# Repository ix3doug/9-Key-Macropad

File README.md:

# 9-Key-Macropad
A 9 Key Macropad for use with F13-F22 key functions. Powered by an RP2040 Microcontroller

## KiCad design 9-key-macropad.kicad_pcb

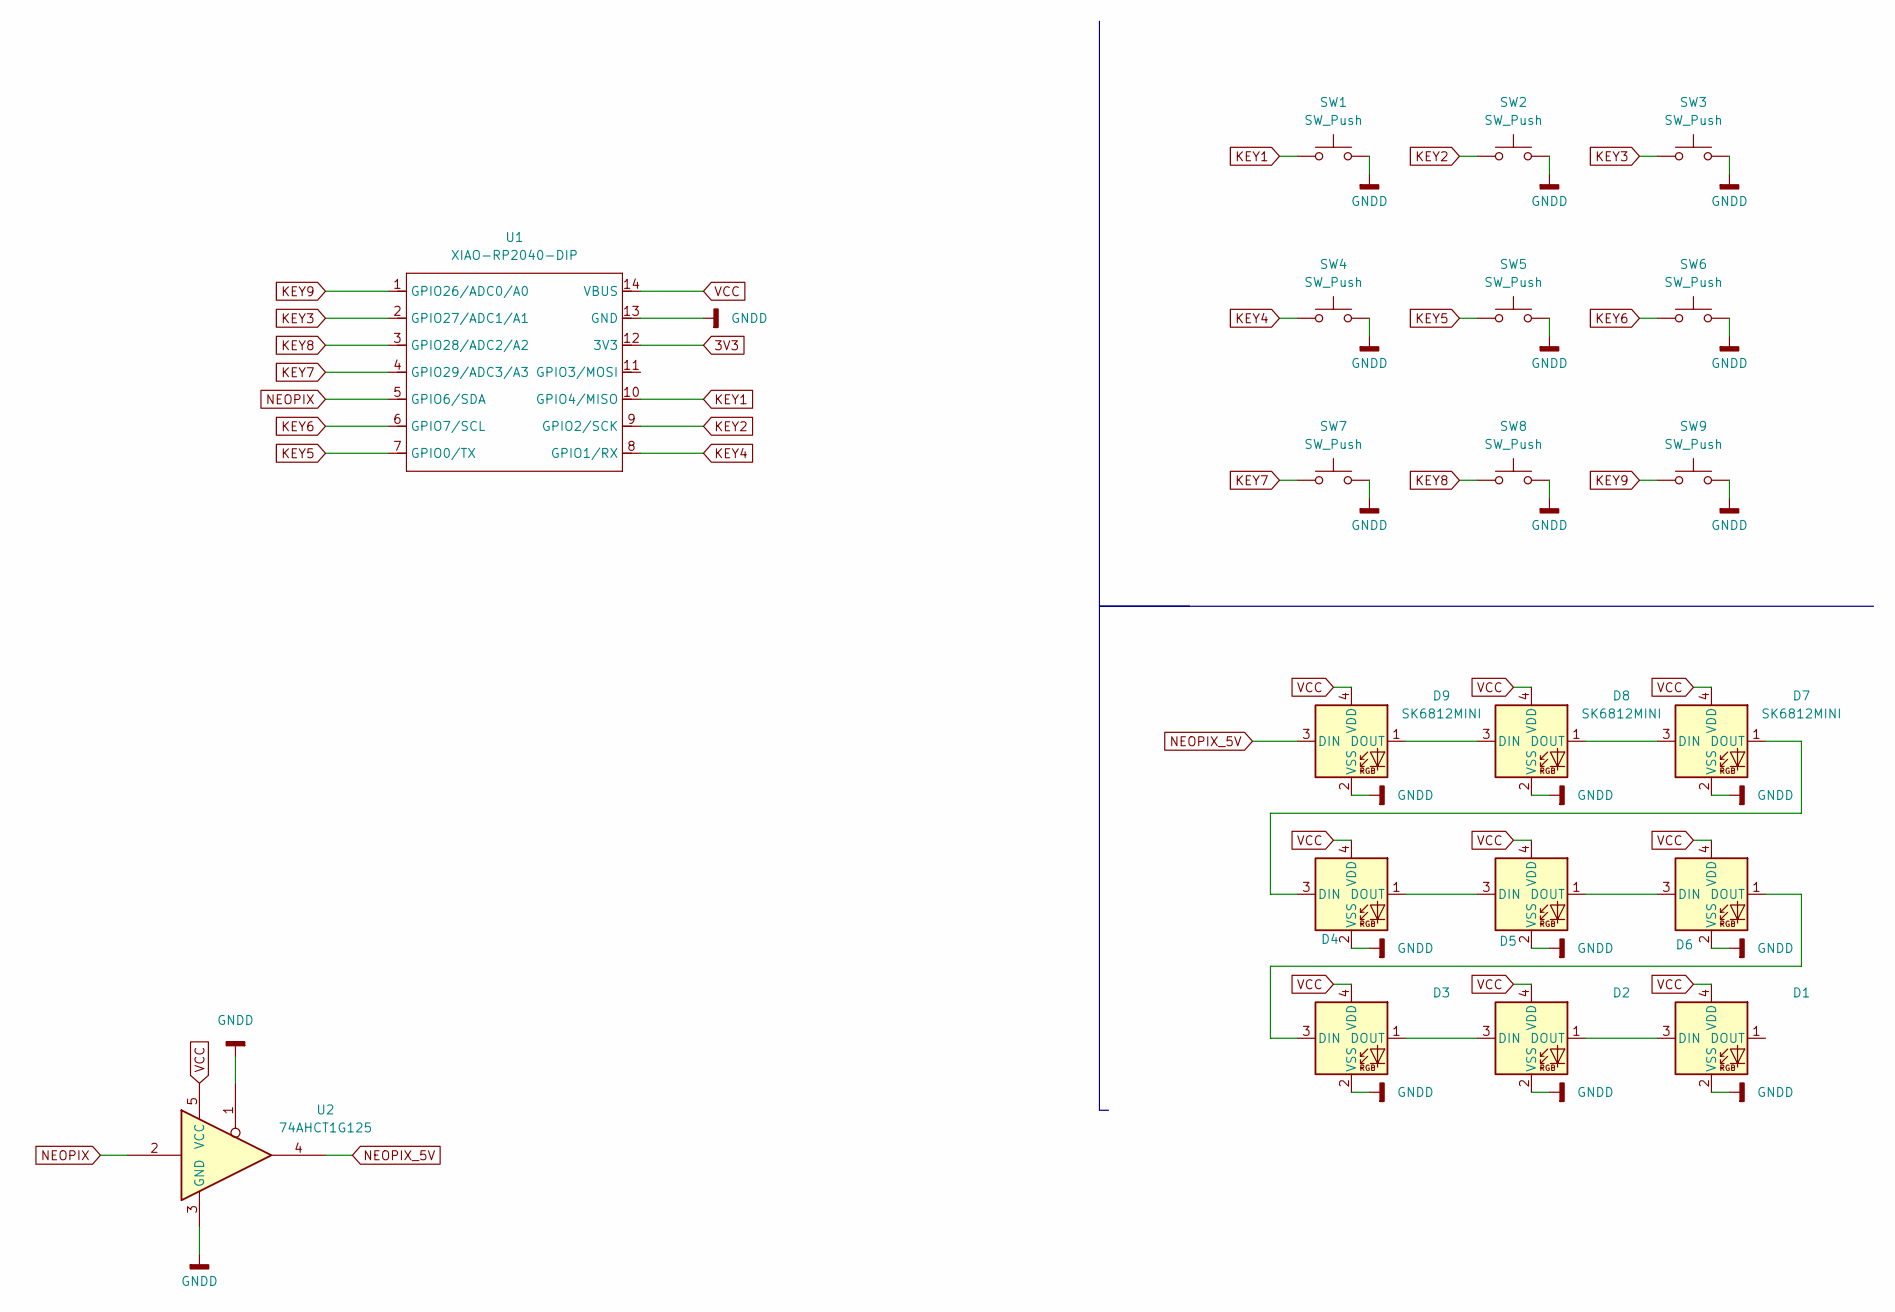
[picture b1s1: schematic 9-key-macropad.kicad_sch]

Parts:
D1, D2, D3, D4, D5, D6, D7, D8, D9: SK6812MINI; LED_SK6812MINI_PLCC4_3.5x3.5mm_P1.75mm
SW1, SW2, SW3, SW4, SW5, SW6, SW7, SW8, SW9: SW_Push; SW_Cherry_MX_1.00u_Plate
U1: XIAO-RP2040-DIP
U2: 74AHCT1G125; SOT95P280X145-5N

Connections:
3V3: U1.12 (3V3)
GNDD: D1.2 (VSS), D2.2 (VSS), D3.2 (VSS), D4.2 (VSS), D5.2 (VSS), D6.2 (VSS), D7.2 (VSS), D8.2 (VSS), D9.2 (VSS), SW1.2, SW2.2, SW3.2, SW4.2, SW5.2, SW6.2, SW7.2, SW8.2, SW9.2, U1.13 (GND), U2.1, U2.3 (GND)
KEY1: SW1.1, U1.10 (GPIO4/MISO)
KEY2: SW2.1, U1.9 (GPIO2/SCK)
KEY3: SW3.1, U1.2 (GPIO27/ADC1/A1)
KEY4: SW4.1, U1.8 (GPIO1/RX)
KEY5: SW5.1, U1.7 (GPIO0/TX)
KEY6: SW6.1, U1.6 (GPIO7/SCL)
KEY7: SW7.1, U1.4 (GPIO29/ADC3/A3)
KEY8: SW8.1, U1.3 (GPIO28/ADC2/A2)
KEY9: SW9.1, U1.1 (GPIO26/ADC0/A0)
NEOPIX: U1.5 (GPIO6/SDA), U2.2
NEOPIX_5V: D9.3 (DIN), U2.4
unnamed: D1.3 (DIN), D2.1 (DOUT)
unnamed: D2.3 (DIN), D3.1 (DOUT)
unnamed: D3.3 (DIN), D6.1 (DOUT)
unnamed: D4.3 (DIN), D7.1 (DOUT)
unnamed: D4.1 (DOUT), D5.3 (DIN)
unnamed: D5.1 (DOUT), D6.3 (DIN)
unnamed: D7.3 (DIN), D8.1 (DOUT)
unnamed: D8.3 (DIN), D9.1 (DOUT)
VCC: D1.4 (VDD), D2.4 (VDD), D3.4 (VDD), D4.4 (VDD), D5.4 (VDD), D6.4 (VDD), D7.4 (VDD), D8.4 (VDD), D9.4 (VDD), U1.14 (VBUS), U2.5 (VCC)

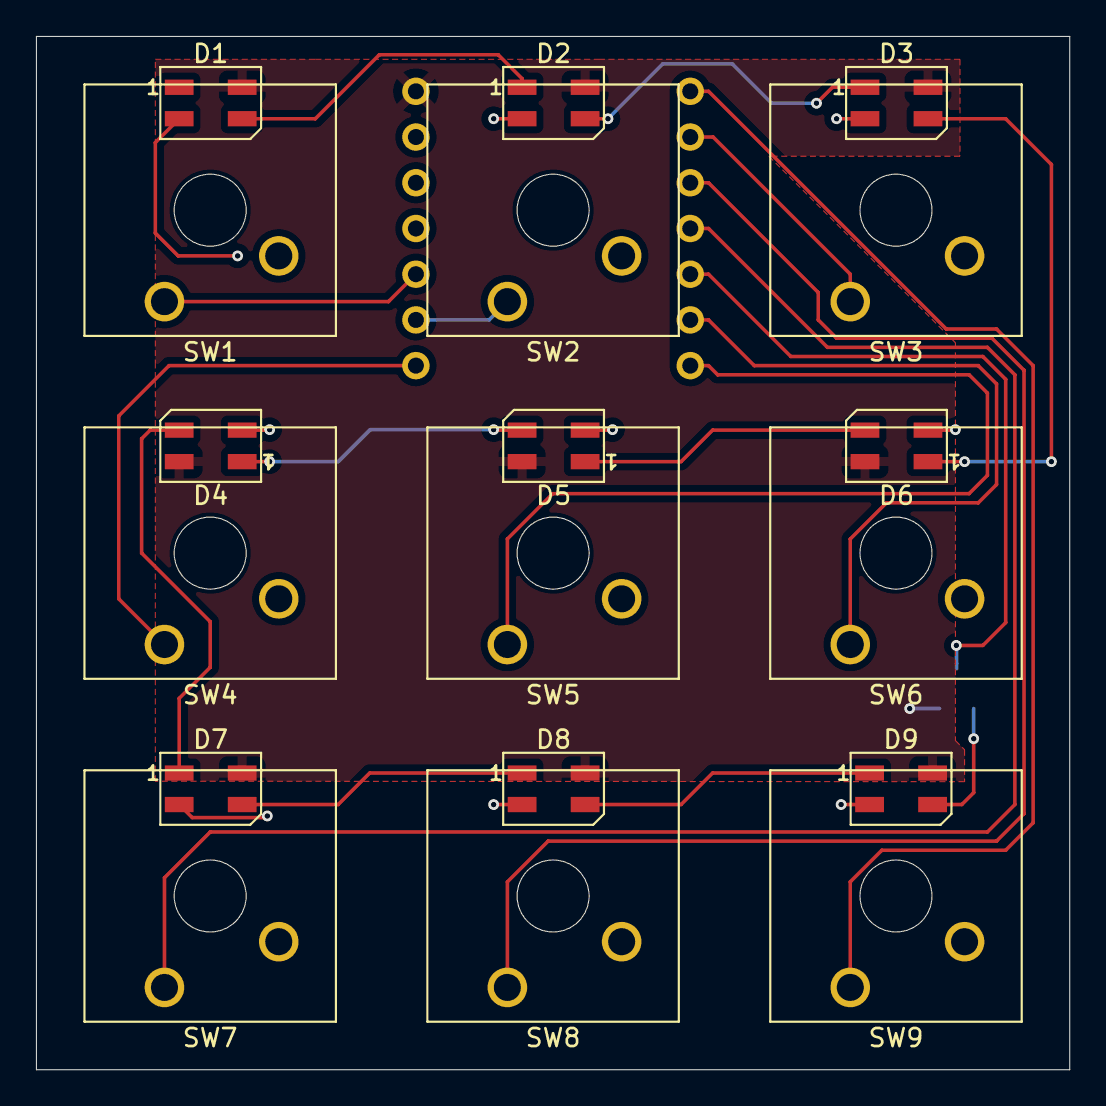
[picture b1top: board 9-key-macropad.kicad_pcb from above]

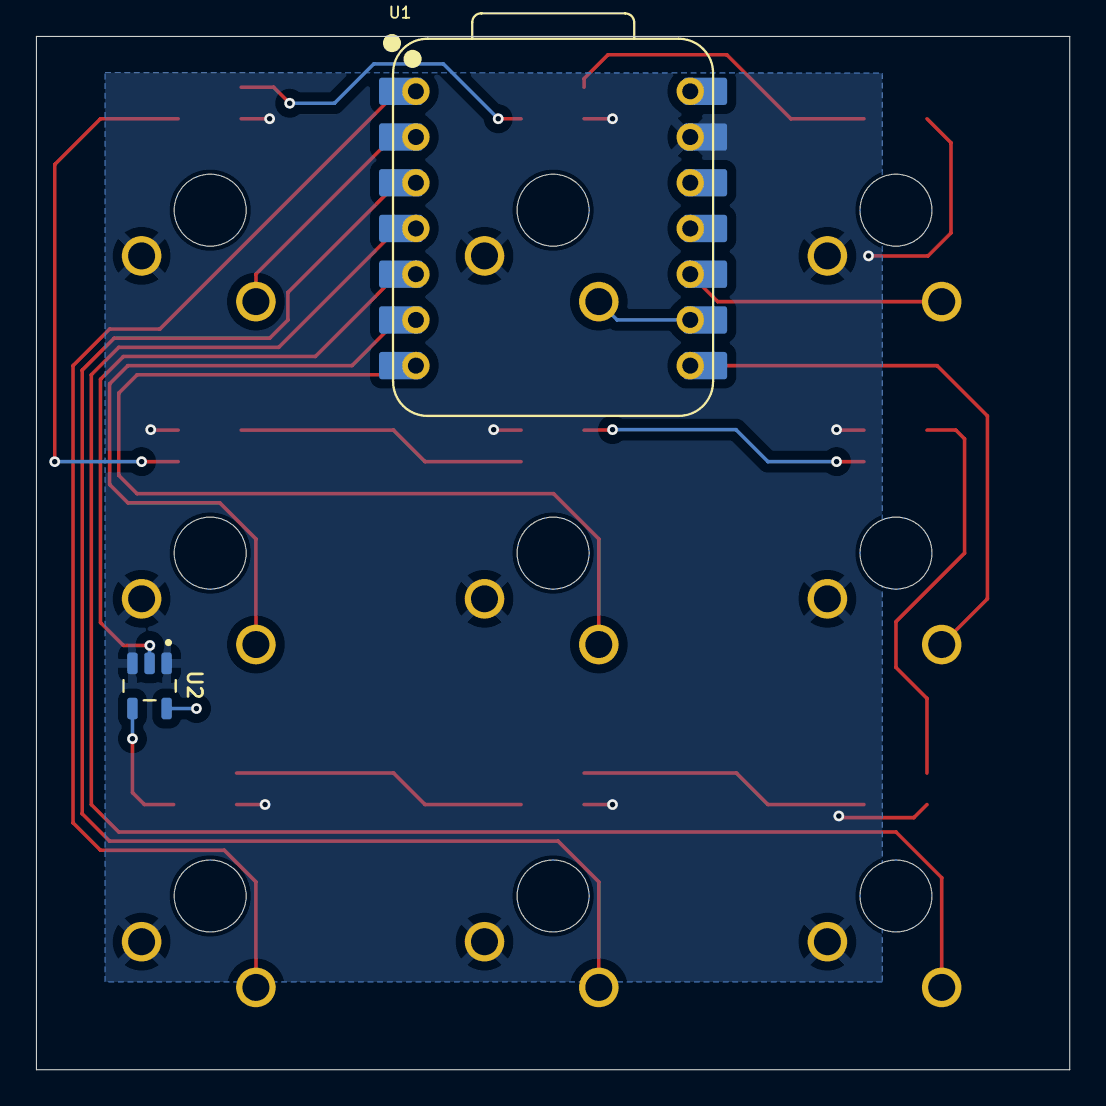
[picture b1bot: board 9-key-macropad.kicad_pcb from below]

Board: 2 copper layers, 57.4 x 57.4 mm, 20 parts (2 on the bottom side), 21 nets.

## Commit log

2025-09-22 Create LICENSE
2025-09-22 Add initial 9-key-macropad KiCad project files and Submodules
    Added schematic, PCB, and project files for the 9-key macropad. Included submodules for OPL_Kicad_Library and kiswitch libraries to support component footprints and symbols.
    No Setup or Configuration of Project at This Point, Only Addition of Dependencies.
2025-09-22 Add Project-Specific KiCad footprint and symbol library tables
    Introduces fp-lib-table and sym-lib-table files to configure project-specific footprint and symbol libraries for KiCad, including Cherry MX switch and Seeed Studio XIAO Series libraries.
2025-09-22 Controller and Switch Schematic Assignments
    Added the Seeed Studio XIAO-RP2040-DIP module and generic push button switch symbols to the schematic. Updated project and schematic files to include symbol definitions, global labels for keys, and w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
2025-09-23 Add Step-Up library and update PCB + SCM
    Added SN74AHCT1G125DBVR symbol, footprint, STEP model, and documentation to the libraries directory. Updated 9-key-macropad PCB, schematic, and project files to include new components and connections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
2025-09-23 Update switch and LED positions on PCB
    Repositioned Cherry MX switches and SK6812MINI LEDs to new coordinates and orientations on the 9-key macropad PCB. This change likely reflects a new layout or mechanical design for improved ergonomic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
2025-09-23 Rearrange key switches and LEDs, update net assignments
    Moved key switches and SK6812MINI LEDs to new positions for improved layout. Updated net assignments for GPIO pins to match new key mapping and corrected NEOPIX and unconnected net references. Adjust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
2025-09-23 Continued Board Development
    Reworked Schematic for better trace layout and started adding traces to PCB design
2025-09-23 Update net assignments and LED footprints
    Reorganized net numbers and names for clarity and consistency, updated LED SK6812MINI footprints and pad orientations, and corrected net connections for keys and LEDs. These changes improve schematic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
2025-09-23 PCB and schematic design complete pending review
    Completed the design for the PCB and Schematic.
    Holding off having it printed until I can find a professional to review it.
